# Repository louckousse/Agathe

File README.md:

# Agathe
Another Alice-clone

Following a 65% approach with close arrow-cluster and support for rotary encoders

All the pcb files are created in Kicad, you can find everything in the root folder.

## Development

clone this repos with submodules
```
git clone --recurse-submodule https://github.com/louckousse/Agathe.git
```

## Building
When building this keyboard if you want to use the one rotary encoders you'll have to solder the jumper between the middle pad to the pad 1. If you want to use multiple, solder the other way around and check [this pr](https://github.com/qmk/qmk_firmware/pull/7209).

## Keymap
You can find the keymap under my [QMK fork](https://github.com/louckousse/keymaps/tree/main/agathe).

# License
This work is licensed under a [Attribution-NonCommercial-ShareAlike 4.0 International (CC BY-NC-SA 4.0)](https://creativecommons.org/licenses/by-nc-sa/4.0/).

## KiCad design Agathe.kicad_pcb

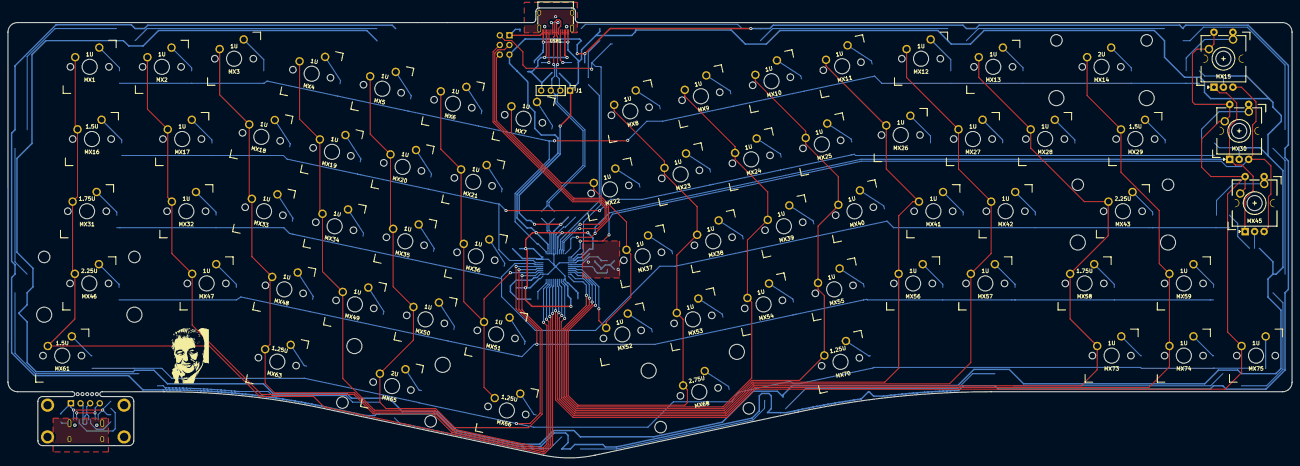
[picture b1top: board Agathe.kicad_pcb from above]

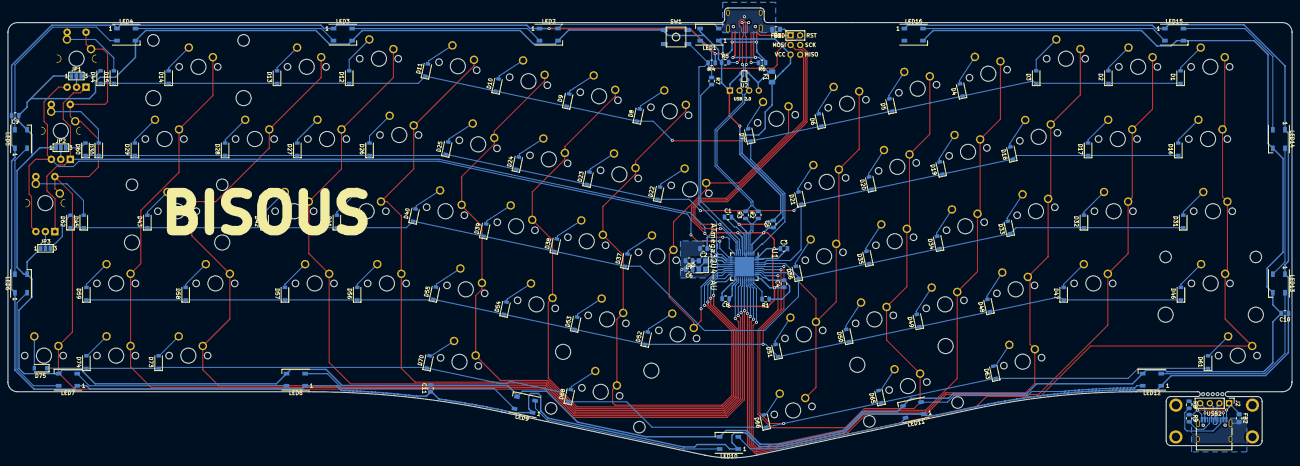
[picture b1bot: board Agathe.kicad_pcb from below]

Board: 2 copper layers, 338.8 x 118.7 mm, 188 parts (119 on the bottom side), 136 nets.

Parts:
C1: 1uF; C_0805_2012Metric
C2, C3, C4, C8, C9, C10, C11: 0.1uF; C_0805_2012Metric
C5: 10uF; C_0805_2012Metric
C6, C7: 22pF; C_0805_2012Metric
D1, D2, D3, D4, D5, D6, D7, D8, D9, D10, D11, D12, D13, D14, D15, D16, D17, D18, D19, D20, D21, D22, D23, D24, D25, D26, D27, D28, D29, D30, D31, D32, D33, D34, D35, D36, D37, D38, D39, D40, D41, D42, D43, D44, D45, D46, D47, D48, D49, D50, D51, D52, D53, D54, D55, D56, D57, D58, D59, D60, D61, D62, D63, D65, D66, D68, D70, D73, D74, D75: D_Small; D_SOD-123
F1: 500mA; Fuse_1206_3216Metric
FB1, FB2: Ferrite_Bead_Small; L_0805_2012Metric_Pad1.15x1.40mm_HandSolder
J1, J2: Conn_01x04_Female; PinHeader_1x04_P2.54mm_Vertical
J3: AVR-ISP-6; Reset_Pretty-Mask
JP1, JP2, JP3: SolderJumper_3_Open; SolderJumper-3_P1.3mm_Open_Pad1.0x1.5mm_NumberLabels
LED1, LED2, LED3, LED4, LED5, LED6, LED7, LED8, LED9, LED10, LED11, LED12, LED13, LED14, LED15, LED16: WS2812B; LED_WS2812B_PLCC4_5.0x5.0mm_P3.2mm
MX1, MX2, MX3, MX4, MX5, MX6, MX7, MX8, MX9, MX10, MX11, MX12, MX13, MX17, MX18, MX19, MX20, MX21, MX22, MX23, MX24, MX25, MX26, MX27, MX28, MX32, MX33, MX34, MX35, MX36, MX37, MX38, MX39, MX40, MX41, MX42, MX47, MX48, MX49, MX50, MX51, MX52, MX53, MX54, MX55, MX56, MX57, MX59, MX73, MX74, MX75: MX-NoLED; mx_1u
MX14: MX-NoLED; mx_2u
MX15, MX30, MX45: Rotary_Encoder_Switch; rotary_x_MX
MX16, MX29, MX61: MX-NoLED; mx_15u
MX31, MX58: MX-NoLED; mx_175u
MX43, MX46: MX-NoLED; mx_225u
MX63, MX66, MX70: MX-NoLED; mx_125u
MX65: MX-NoLED; mx_2ureverse
MX68: MX-NoLED; mx_275u_reverse
R1, R4: 10k; R_0805_2012Metric
R2, R3: 22; R_0805_2012Metric
R5, R6, R8, R9: 5.1k; R_0805_2012Metric
R7: 330; R_0805_2012Metric
SW1: SW_Push; SKQG-1155865
U1: ATmega32U4-AU; QFN-44-1EP_7x7mm_P0.5mm_EP5.2x5.2mm
U2: PRTR5V0U2X; SOT143B
USB1, USB2: USB_C_Receptacle_USB2.0; USB_C_Receptacle_HRO_TYPE-C-31-M-12
Y1: 16MHz; Crystal_SMD_3225-4Pin_3.2x2.5mm

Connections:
+5V: C2.1, C3.1, C4.1, C5.1, C8.1, C9.2, C10.1, C11.1, F1.1, J3.2, LED1.1, LED2.1, LED3.1, LED4.1, LED5.1, LED6.1, LED7.1, LED8.1, LED9.1, LED10.1, LED11.1, LED12.1, LED13.1, LED14.1, LED15.1, LED16.1, R4.1, U1.2, U1.7, U1.14, U1.24, U1.34, U1.44
COL0: MX1.1, MX16.1, MX31.1, MX46.1, MX61.1, U1.29
COL1: MX2.1, MX17.1, MX32.1, MX47.1, U1.30
COL2: MX3.1, MX18.1, MX33.1, MX48.1, MX63.1, U1.31
COL3: MX4.1, MX19.1, MX34.1, MX49.1, U1.32
COL4: MX5.1, MX20.1, MX35.1, MX50.1, MX65.1, U1.36
COL5: MX6.1, MX21.1, MX36.1, MX51.1, MX66.1, U1.37
COL6: MX7.1, MX22.1, MX37.1, MX52.1, U1.18
COL7: MX8.1, MX23.1, MX38.1, MX53.1, MX68.1, U1.19
COL8: MX9.1, MX24.1, MX39.1, MX54.1, U1.20
COL9: MX10.1, MX25.1, MX40.1, MX55.1, MX70.1, U1.21
COL10: MX11.1, MX26.1, MX41.1, MX56.1, U1.22
COL11: MX12.1, MX27.1, MX42.1, MX57.1, U1.25
COL12: MX13.1, MX28.1, MX43.1, MX58.1, MX73.1, U1.26
COL13: MX14.1, MX29.1, MX59.1, MX74.1, U1.27
COL14: MX15.S2, MX30.S2, MX45.S2, MX75.1, U1.28
D+: R3.1, U1.4
D-: R2.1, U1.3
DN: J1.3, R2.2, U2.3, USB1.A7, USB1.B7
DP: J1.2, R3.2, U2.2, USB1.A6, USB1.B6
ETH: FB2.2, USB2.S1
Earth: FB1.2, USB1.S1
GND: C1.2, C2.2, C3.2, C4.2, C5.2, C6.2, C7.2, C8.2, C9.1, C10.2, C11.2, FB1.1, J1.1, J3.6, JP1.1, JP2.1, JP3.1, LED1.3, LED2.3, LED3.3, LED4.3, LED5.3, LED6.3, LED7.3, LED8.3, LED9.3, LED10.3, LED11.3, LED12.3, LED13.3, LED14.3, LED15.3, LED16.3, R1.1, R5.1, R6.1, SW1.1, U1.5, U1.15, U1.23, U1.35, U1.43, U1.45, U2.1, USB1.A1, USB1.A12, USB1.B1, USB1.B12, Y1.2, Y1.4
LED: R7.2, U1.8
MISO: J3.1, MX15.A, MX30.A, MX45.A, U1.11
MOSI: J3.4, U1.10
unnamed: C1.1, U1.6
unnamed: D1.2, MX1.2
unnamed: D2.2, MX2.2
unnamed: D3.2, MX3.2
unnamed: D4.2, MX4.2
unnamed: D5.2, MX5.2
unnamed: D6.2, MX6.2
unnamed: D7.2, MX7.2
unnamed: D8.2, MX8.2
unnamed: D9.2, MX9.2
unnamed: D10.2, MX10.2
unnamed: D11.2, MX11.2
unnamed: D12.2, MX12.2
unnamed: D13.2, MX13.2
unnamed: D14.2, MX14.2
unnamed: D15.2, MX15.S1
unnamed: D16.2, MX16.2
unnamed: D17.2, MX17.2
unnamed: D18.2, MX18.2
unnamed: D19.2, MX19.2
unnamed: D20.2, MX20.2
unnamed: D21.2, MX21.2
unnamed: D22.2, MX22.2
unnamed: D23.2, MX23.2
unnamed: D24.2, MX24.2
unnamed: D25.2, MX25.2
unnamed: D26.2, MX26.2
unnamed: D27.2, MX27.2
unnamed: D28.2, MX28.2
unnamed: D29.2, MX29.2
unnamed: D30.2, MX30.S1
unnamed: D31.2, MX31.2
unnamed: D32.2, MX32.2
unnamed: D33.2, MX33.2
unnamed: D34.2, MX34.2
unnamed: D35.2, MX35.2
unnamed: D36.2, MX36.2
unnamed: D37.2, MX37.2
unnamed: D38.2, MX38.2
unnamed: D39.2, MX39.2
unnamed: D40.2, MX40.2
unnamed: D41.2, MX41.2
unnamed: D42.2, MX42.2
unnamed: D43.2, MX43.2
unnamed: D44.2, JP1.3
unnamed: D45.2, MX45.S1
unnamed: D46.2, MX46.2
unnamed: D47.2, MX47.2
unnamed: D48.2, MX48.2
unnamed: D49.2, MX49.2
unnamed: D50.2, MX50.2
unnamed: D51.2, MX51.2
unnamed: D52.2, MX52.2
unnamed: D53.2, MX53.2
unnamed: D54.2, MX54.2
unnamed: D55.2, MX55.2
unnamed: D56.2, MX56.2
unnamed: D57.2, MX57.2
unnamed: D58.2, MX58.2
unnamed: D59.2, MX59.2
unnamed: D60.2, JP2.3
unnamed: D61.2, MX61.2
unnamed: D62.2, JP3.3
unnamed: D63.2, MX63.2
unnamed: D65.2, MX65.2
unnamed: D66.2, MX66.2
unnamed: D68.2, MX68.2
unnamed: D70.2, MX70.2
unnamed: D73.2, MX73.2
unnamed: D74.2, MX74.2
unnamed: D75.2, MX75.2
unnamed: FB2.1, J2.1, R8.1, R9.1, USB2.A1, USB2.A12, USB2.B1, USB2.B12
unnamed: J2.2, USB2.A6, USB2.B6
unnamed: J2.3, USB2.A7, USB2.B7
unnamed: J2.4, USB2.A4, USB2.A9, USB2.B4, USB2.B9
unnamed: JP1.2, MX15.C
unnamed: JP2.2, MX30.C
unnamed: JP3.2, MX45.C
unnamed: LED1.2, LED2.4
unnamed: LED1.4, R7.1
unnamed: LED2.2, LED3.4
unnamed: LED3.2, LED4.4
unnamed: LED4.2, LED5.4
unnamed: LED5.2, LED6.4
unnamed: LED6.2, LED7.4
unnamed: LED7.2, LED8.4
unnamed: LED8.2, LED9.4
unnamed: LED10.2, LED11.4
unnamed: LED9.2, LED10.4
unnamed: LED11.2, LED12.4
unnamed: LED12.2, LED13.4
unnamed: LED13.2, LED14.4
unnamed: LED14.2, LED15.4
unnamed: LED15.2, LED16.4
unnamed: R1.2, U1.33
unnamed: R5.2, USB1.A5
unnamed: R6.2, USB1.B5
unnamed: R8.2, USB2.B5
unnamed: R9.2, USB2.A5
ROTB: MX15.B, MX30.B, MX45.B, U1.12
ROW0: D1.1, D2.1, D3.1, D4.1, D5.1, D6.1, D7.1, D8.1, D9.1, D10.1, D11.1, D12.1, D13.1, D14.1, D15.1, D44.1, U1.1
ROW1: D16.1, D17.1, D18.1, D19.1, D20.1, D21.1, D22.1, D23.1, D24.1, D25.1, D26.1, D27.1, D28.1, D29.1, D30.1, D60.1, U1.41
ROW2: D31.1, D32.1, D33.1, D34.1, D35.1, D36.1, D37.1, D38.1, D39.1, D40.1, D41.1, D42.1, D43.1, D45.1, D62.1, U1.40
ROW3: D46.1, D47.1, D48.1, D49.1, D50.1, D51.1, D52.1, D53.1, D54.1, D55.1, D56.1, D57.1, D58.1, D59.1, U1.39
ROW4: D61.1, D63.1, D65.1, D66.1, D68.1, D70.1, D73.1, D74.1, D75.1, U1.38
RST: J3.5, R4.2, SW1.2, U1.13
SCK: J3.3, U1.9
VCC: F1.2, J1.4, U2.4, USB1.A4, USB1.A9, USB1.B4, USB1.B9
XTAL1: C6.1, U1.17, Y1.1
XTAL2: C7.1, U1.16, Y1.3

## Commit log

2020-04-26 Create the initial schema
2020-04-26 Current layout before deleted keys
2020-04-26 day 2 of work
    MCU and USB routed
    All switch routed between them
    Todo: connect row and column to MCU
2020-04-27 Route everything
2020-04-28 change the enter footprint
2020-05-01 Add a proper usb-c
2020-05-01 Add .dxf files
2020-05-02 Add rotary encoder support
2020-05-02 Add cache lib
2020-05-02 Add underglow
2020-05-09 Update footprints for switch
2020-09-30 Change var KEEBS to KIPRJMOD
2020-10-03 Change var KEEBS to KIPRJMOD (#1)
2020-10-04 Fix librairie path
2020-10-04 Add submodule explanation
2020-10-04 add render view
2020-10-04 Rerouting around USB-C connector
2020-10-06 add 2 breakout header for VCC and GND
2020-10-07 add 2 breakout header for VCC and GND (#8)
    * Add submodule explanation
    * add render view
    * Rerouting around USB-C connector
    * WIP
    * end
    * end
2020-10-07 Fix lib path (#3)
    * Change var KEEBS to KIPRJMOD
    * Fix librairie path
2020-10-07 correct some routes
2020-10-07 add fp-info-cache to the gitignore
2020-10-07 add value for rst resistor and crystal (#2)
2020-10-08 :arrow_up: Upgrade Keebio-Parts.pretty submodule to latest master
2020-10-08 Realign J3 and J2. Reroute D- around J4
2020-10-08 Revert ":arrow_up: Upgrade Keebio-Parts.pretty submodule to latest master"
    This reverts commit 1108f9b439529876e9ef4f3663b1b982b7d3c81e.
2020-10-08 add louckousse-kicad
2020-10-09 Move J2 to top
2020-10-10 Upgrade Keebio-Parts.pretty, add louckousse-kicad submodules (#10)
    * :arrow_up: Upgrade Keebio-Parts.pretty submodule to latest master
    * add louckousse-kicad
2020-10-10 move breakout to the top
2020-10-10 add cc.pretty
2020-10-10 Add Agathe lib
2020-10-10 reverse vcc and gnd on leds (#9)
2020-10-18 add a capacitor
2020-10-24 update shematics
    add spi interface
    add 6 leds
    change the esp
2020-10-25 j'ai putain de tout refait putain
2020-10-27 add some stuff after a review from @plut0nium
    Some new feature from the @masterzen blog article
    http://www.masterzen.fr/2020/10/20/designing-a-keyboard-part3/
2020-10-28 add a breakable usb port and matrix encoder
2020-10-31 add matrice rotary possibilities
2020-11-14 move the daughterboard at the bottom and change the mcu
2020-11-21 replace the mcu by an elite-c in the schema
2020-11-21 pcb adapted for elite-c and th diodes
2020-11-22 update my kicad lib
2020-11-22 add a new outline
2020-11-27 elite-c horizontal
2020-11-28 new outline
2020-12-20 top mount usb-port
2020-12-20 update submodule
